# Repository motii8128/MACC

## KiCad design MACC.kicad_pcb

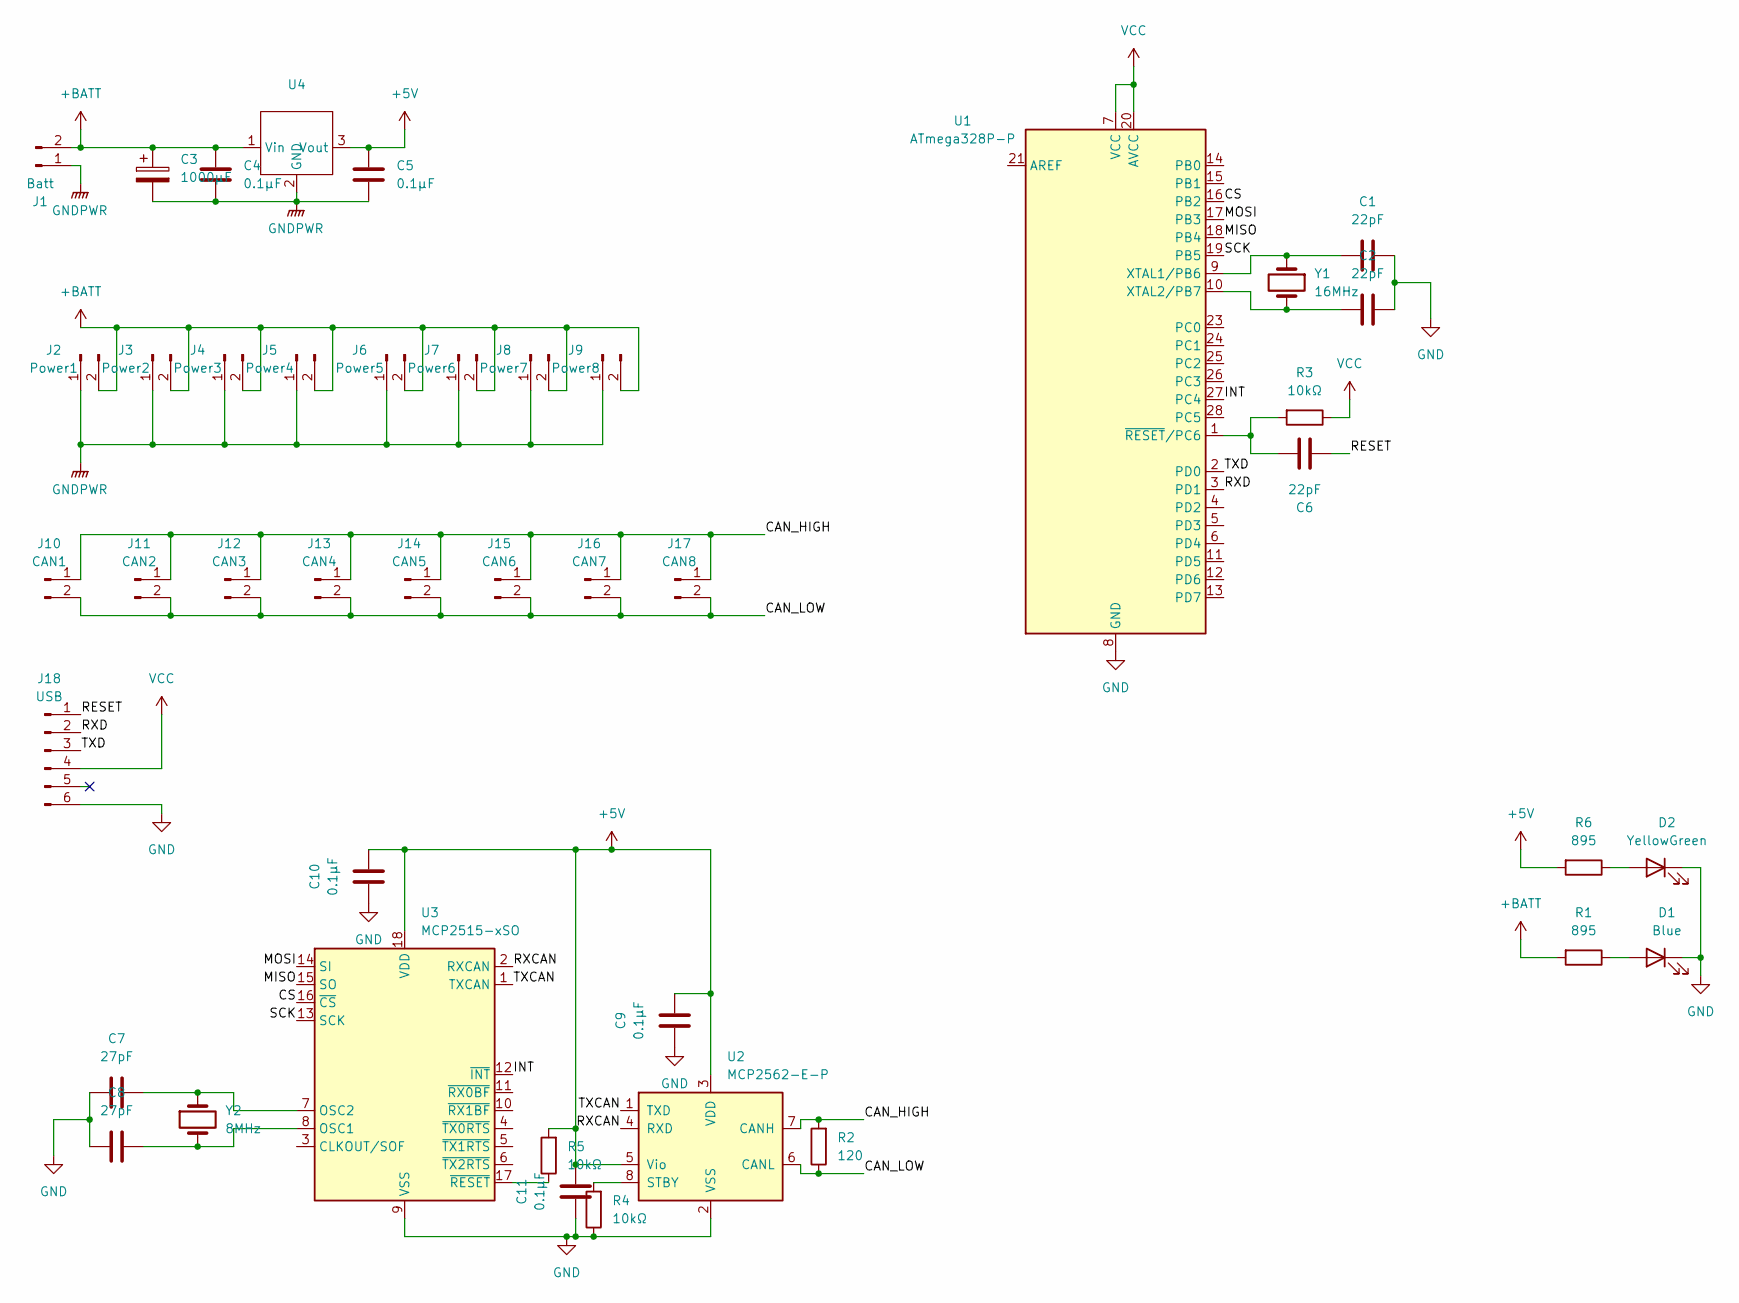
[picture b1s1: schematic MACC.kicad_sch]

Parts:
C1, C2, C6: 22pF; C_Disc_D3.0mm_W2.0mm_P2.50mm
C3: 1000μF; C_Radial_D12.5mm_H25.0mm_P5.00mm
C4, C5, C9, C10, C11: 0.1μF; C_Disc_D3.0mm_W2.0mm_P2.50mm
C7, C8: 27pF; C_Disc_D3.0mm_W2.0mm_P2.50mm
D1: Blue; LED_D3.0mm
D2: YellowGreen; LED_D3.0mm
J1: Batt; AMASS_XT60-M_1x02_P7.20mm_Vertical
J2: Power1; AMASS_XT30U-F_1x02_P5.0mm_Vertical
J3: Power2; AMASS_XT30U-F_1x02_P5.0mm_Vertical
J4: Power3; AMASS_XT30U-F_1x02_P5.0mm_Vertical
J5: Power4; AMASS_XT30U-F_1x02_P5.0mm_Vertical
J6: Power5; AMASS_XT30U-F_1x02_P5.0mm_Vertical
J7: Power6; AMASS_XT30U-F_1x02_P5.0mm_Vertical
J8: Power7; AMASS_XT30U-F_1x02_P5.0mm_Vertical
J9: Power8; AMASS_XT30U-F_1x02_P5.0mm_Vertical
J10: CAN1; JST_XH_B2B-XH-A_1x02_P2.50mm_Vertical
J11: CAN2; JST_XH_B2B-XH-A_1x02_P2.50mm_Vertical
J12: CAN3; JST_XH_B2B-XH-A_1x02_P2.50mm_Vertical
J13: CAN4; JST_XH_B2B-XH-A_1x02_P2.50mm_Vertical
J14: CAN5; JST_XH_B2B-XH-A_1x02_P2.50mm_Vertical
J15: CAN6; JST_XH_B2B-XH-A_1x02_P2.50mm_Vertical
J16: CAN7; JST_XH_B2B-XH-A_1x02_P2.50mm_Vertical
J17: CAN8; JST_XH_B2B-XH-A_1x02_P2.50mm_Vertical
J18: USB; PinHeader_1x06_P2.54mm_Vertical
R1, R6: 895; R_Axial_DIN0207_L6.3mm_D2.5mm_P10.16mm_Horizontal
R2: 120; R_Axial_DIN0207_L6.3mm_D2.5mm_P10.16mm_Horizontal
R3, R4, R5: 10kΩ; R_Axial_DIN0207_L6.3mm_D2.5mm_P10.16mm_Horizontal
U1: ATmega328P-P; DIP-28_W7.62mm
U2: MCP2562-E-P; DIP-8_W7.62mm
U3: MCP2515-xSO; DIP-18_W7.62mm
U4: m78ar033-1
Y1: 16MHz; Crystal_HC49-4H_Vertical
Y2: 8MHz; Crystal_HC49-4H_Vertical

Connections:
+5V: C5.1, C9.1, C10.1, C11.1, R5.2, R6.2, U2.3 (VDD), U2.5 (Vio), U3.18 (VDD), U4.3 (Vout)
+BATT: C3.1, C4.1, J1.2, J2.2, J3.2, J4.2, J5.2, J6.2, J7.2, J8.2, J9.2, R1.2, U4.1 (Vin)
/CAN_HIGH: J10.1, J11.1, J12.1, J13.1, J14.1, J15.1, J16.1, J17.1, R2.2, U2.7 (CANH)
/CAN_LOW: J10.2, J11.2, J12.2, J13.2, J14.2, J15.2, J16.2, J17.2, R2.1, U2.6 (CANL)
/CS: U1.16 (PB2), U3.16 (~CS)
/INT: U1.27 (PC4), U3.12 (~INT)
/MISO: U1.18 (PB4), U3.15 (SO)
/MOSI: U1.17 (PB3), U3.14 (SI)
/RESET: C6.2, J18.1
/RXCAN: U2.4 (RXD), U3.2 (RXCAN)
/RXD: J18.2, U1.3 (PD1)
/SCK: U1.19 (PB5), U3.13 (SCK)
/TXCAN: U2.1 (TXD), U3.1 (TXCAN)
/TXD: J18.3, U1.2 (PD0)
GND: C1.2, C2.2, C7.2, C8.2, C9.2, C10.2, C11.2, D1.1 (K), D2.1 (K), J18.6, R4.1, U1.8 (GND), U1.22 (GND), U2.2 (VSS), U3.9 (VSS)
GNDPWR: C3.2, C4.2, C5.2, J1.1, J2.1, J3.1, J4.1, J5.1, J6.1, J7.1, J8.1, J9.1, U4.2 (GND)
unnamed: D1.2 (A), R1.1
unnamed: D2.2 (A), R6.1
unnamed: C1.1, U1.9 (XTAL1/PB6), Y1.1
unnamed: C2.1, U1.10 (XTAL2/PB7), Y1.2
unnamed: C6.1, R3.2, U1.1 (~RESET/PC6)
unnamed: R4.2, U2.8 (STBY)
unnamed: C8.1, U3.8 (OSC1), Y2.2
unnamed: C7.1, U3.7 (OSC2), Y2.1
unnamed: R5.1, U3.17 (~RESET)
VCC: J18.4, R3.1, U1.7 (VCC), U1.20 (AVCC)

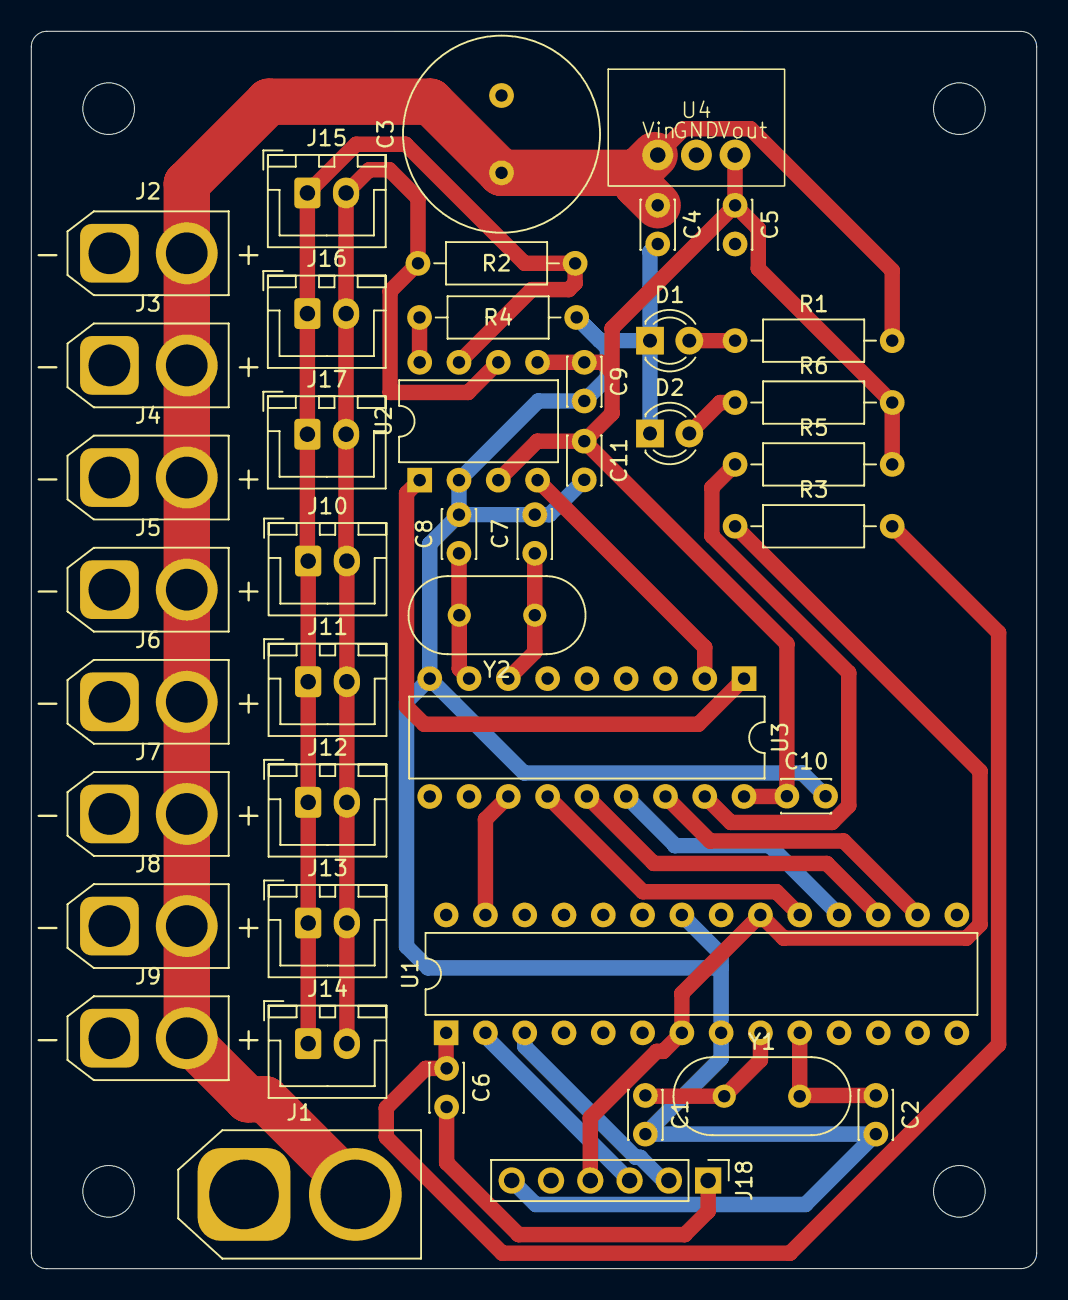
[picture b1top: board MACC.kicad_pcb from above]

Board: 2 copper layers, 65.0 x 80.0 mm, 43 parts (0 on the bottom side), 26 nets.

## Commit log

2025-11-19 upload version 1 data
2025-11-19 Add image to README for MCP & Arduino CAN Controller
